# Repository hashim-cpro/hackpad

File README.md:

<div align="center">
  <a href="https://hackclub.com/highway">
    </img>
  </a>
  
<h1>Hackpad</h1>
</div>
A custom mechanical keypad/macropad built with RP2040 microcontroller featuring 9 Cherry MX switches, a rotary encoder and a OLED. My first ever Hardware project!

## Overview

## Schematic

## PCB

## Case

## Bill of Materials (BOM)

| Component              | Quantity |
| ---------------------- | -------- |
| Custom PCB             | 1x       |
| RP2040 Microcontroller | 1x       |
| Cherry MX Switches     | 6x       |
| EC11 Rotary Encoder    | 1x       |
| 0.91 icnh OLED         | 1x       |
| Front Case             | 1x       |
| Back Case              | 1x       |

## Firmware

Firmware is built using [QMK](https://qmk.fm/). It is pretty basic with only one Layer at the moment, but it is fully functional. I will add more features later.

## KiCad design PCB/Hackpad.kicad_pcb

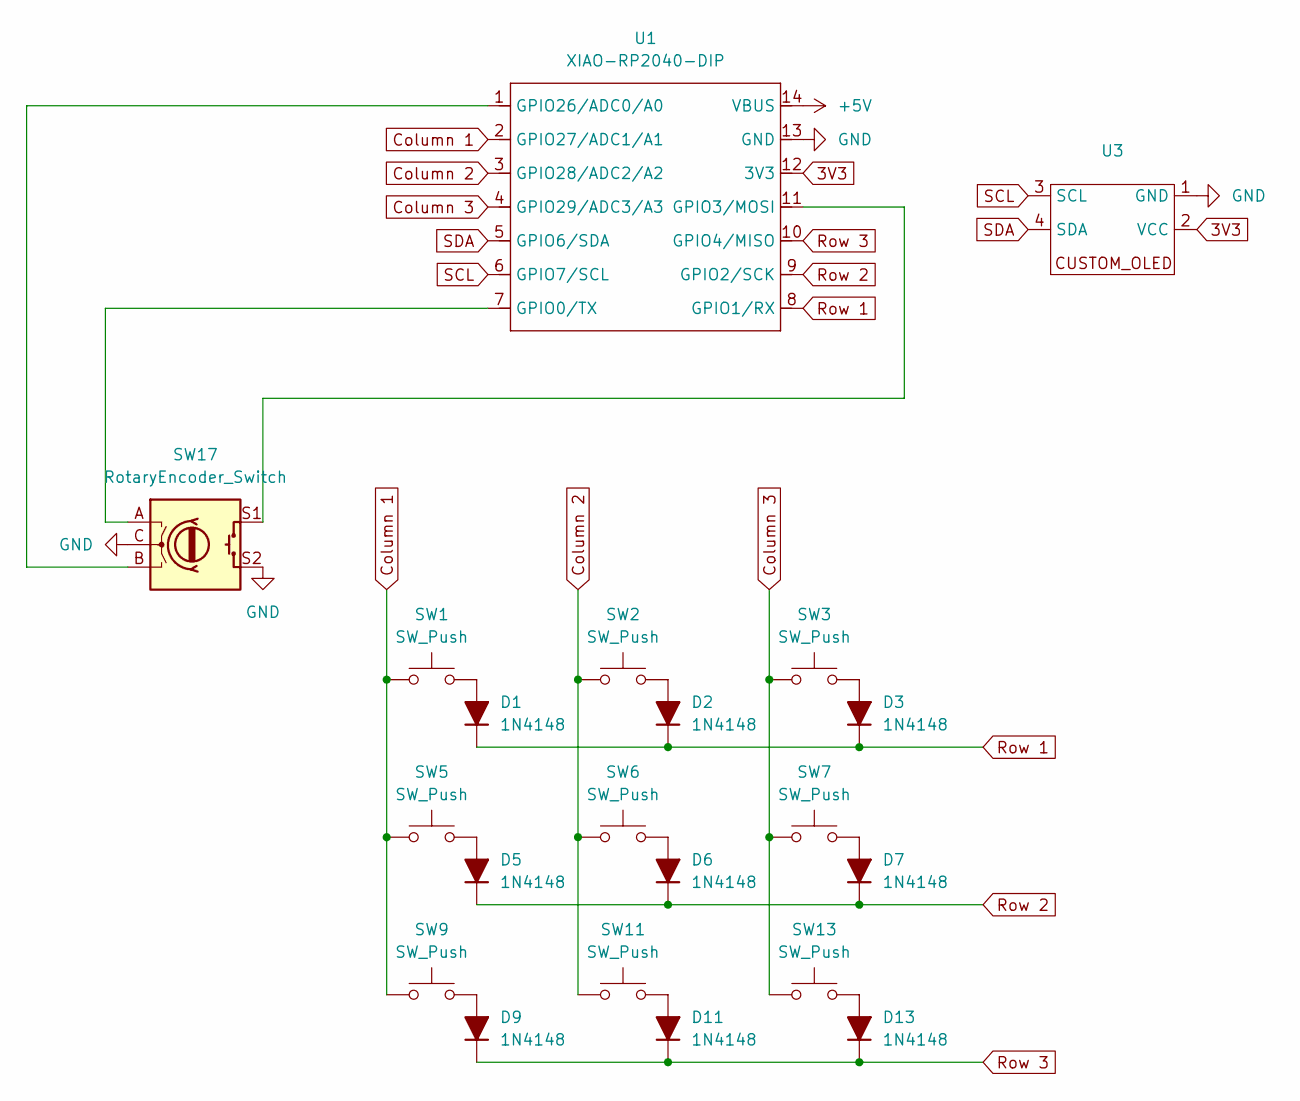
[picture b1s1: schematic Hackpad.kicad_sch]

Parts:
D1, D2, D3, D5, D6, D7, D9, D11, D13: 1N4148; D_DO-35_SOD27_P7.62mm_Horizontal
SW1, SW2, SW3, SW5, SW6, SW7, SW9, SW11, SW13: SW_Push; SW_Cherry_MX_1.00u_PCB
SW17: RotaryEncoder_Switch; RotaryEncoder_Alps_EC11E-Switch_Vertical_H20mm
U1: XIAO-RP2040-DIP
U3: SSD1306-0.91-OLED-4pin-128x32

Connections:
3V3: U1.12 (3V3), U3.2 (VCC); also elsewhere on the board
+5V: U1.14 (VBUS)
Column 1: SW1.1, SW5.1, SW9.1, U1.2 (GPIO27/ADC1/A1)
Column 2: SW2.1, SW6.1, SW11.1, U1.3 (GPIO28/ADC2/A2)
Column 3: SW3.1, SW7.1, SW13.1, U1.4 (GPIO29/ADC3/A3)
GND: SW17.C, SW17.S2, U1.13 (GND), U3.1 (GND); also elsewhere on the board
unnamed: D1.2 (A), SW1.2
unnamed: D2.2 (A), SW2.2
unnamed: D3.2 (A), SW3.2
unnamed: D5.2 (A), SW5.2
unnamed: D6.2 (A), SW6.2
unnamed: D7.2 (A), SW7.2
unnamed: D9.2 (A), SW9.2
unnamed: D11.2 (A), SW11.2
unnamed: D13.2 (A), SW13.2
unnamed: SW17.A, U1.7 (GPIO0/TX)
unnamed: SW17.S1, U1.11 (GPIO3/MOSI)
unnamed: SW17.B, U1.1 (GPIO26/ADC0/A0)
Row 1: D1.1 (K), D2.1 (K), D3.1 (K), U1.8 (GPIO1/RX)
Row 2: D5.1 (K), D6.1 (K), D7.1 (K), U1.9 (GPIO2/SCK)
Row 3: D9.1 (K), D11.1 (K), D13.1 (K), U1.10 (GPIO4/MISO)
SCL: U1.6 (GPIO7/SCL), U3.3 (SCL); also elsewhere on the board
SDA: U1.5 (GPIO6/SDA), U3.4 (SDA); also elsewhere on the board

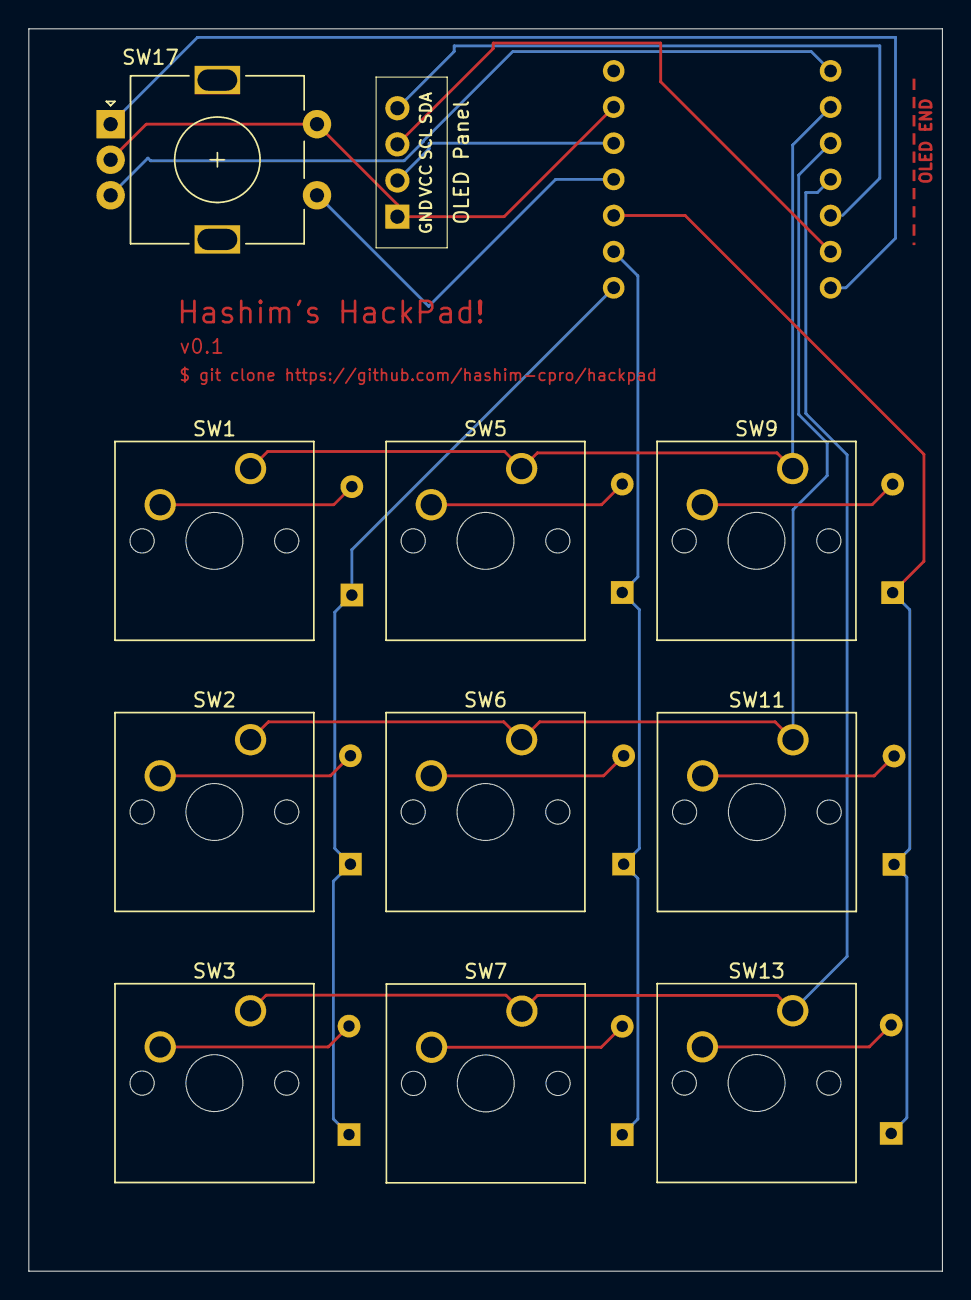
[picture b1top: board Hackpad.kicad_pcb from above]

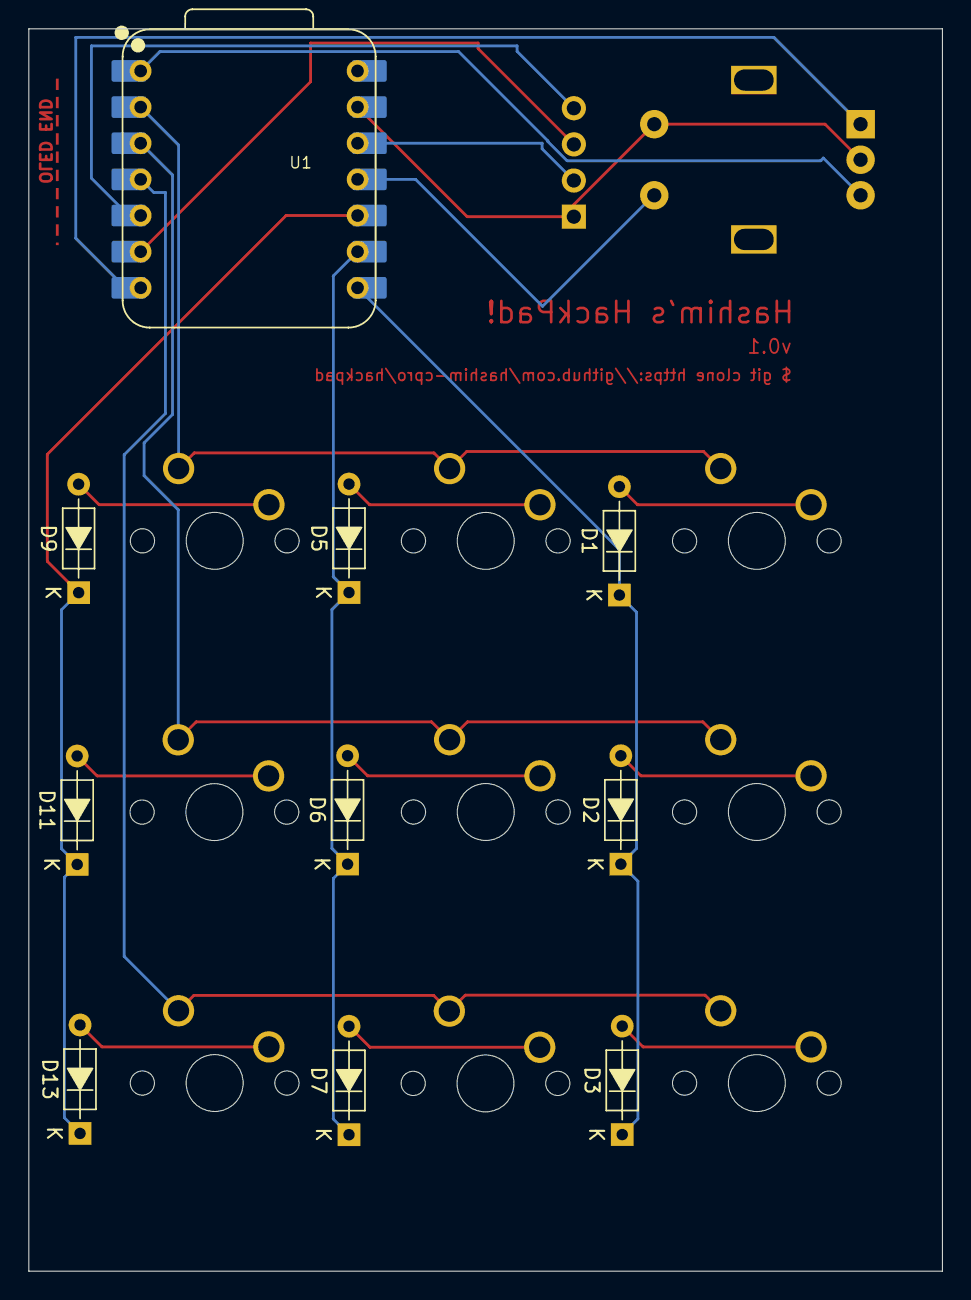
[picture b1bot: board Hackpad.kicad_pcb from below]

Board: 2 copper layers, 64.2 x 87.3 mm, 21 parts (10 on the bottom side), 22 nets.

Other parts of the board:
OLED END: U3; SSD1306-0.91-OLED-4pin-128x32

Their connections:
3V3: OLED END.2 (VCC); also elsewhere on the board
GND: OLED END.1 (GND); also elsewhere on the board
SCL: OLED END.3 (SCL); also elsewhere on the board
SDA: OLED END.4 (SDA); also elsewhere on the board

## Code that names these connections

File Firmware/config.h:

#pragma once

// Matrix configuration
// Columns: GPIO27, GPIO28, GPIO29
// Rows:    GPIO1, GPIO2, GPIO4

// Rotary Encoder configuration
// A: GPIO26
// B: GPIO0
// Switch (S1): GPIO3

// OLED configuration 
// SCL: GPIO7
// SDA: GPIO6

#define MATRIX_ROWS 3 
#define MATRIX_COLS 3 

#define MATRIX_ROW_PINS { GP1, GP2, GP4 }
#define MATRIX_COL_PINS { GP27, GP28, GP29 }


#define DIODE_DIRECTION COL2ROW


#define ENCODER_A_PINS { GP26 }
#define ENCODER_B_PINS { GP0 }
#define ENCODER_RESOLUTION 2 // hope it's correct, if not, change it to 4

#define ENCODER_HAS_SWITCH
#define ENCODER_SWITCH_PIN GP3 

#define OLED_DISPLAY_128X32 
#define OLED_DRIVER_SSD1306 // Common driver for many OLEDs

#define OLED_I2C_ADDR 0x3C // Or 0x3D

#define OLED_SDA_PIN GP6
#define OLED_SCL_PIN GP7

// Optional: OLED timeout to turn off the display after inactivity
// #define OLED_TIMEOUT 30000 // 30 seconds

// Optional: OLED brightness (0-255)
// #define OLED_BRIGHTNESS 128

// Optional: Enable debug features (useful for troubleshooting)
// #define DEBUG_MATRIX_SCAN
// #define DEBUG_ENCODERS
// #define DEBUG_OLED

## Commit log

2025-07-19 add readme
2025-07-19 add firmware
